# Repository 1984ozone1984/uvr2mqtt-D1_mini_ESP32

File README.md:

# UVR2MQTT - UVR1611 DL-Bus to MQTT Gateway

ESP32-based gateway that reads data from a Technische Alternative UVR1611 solar heating controller via DL-Bus and publishes to MQTT with Home Assistant auto-discovery.

## Hardware

- **Board**: Azdelivery D1 Mini ESP32 (ESP32-WROOM-32)
- **Connection**: DL-Bus via optocoupler to GPIO26
- **PCB Files**: KiCad schematic and PCB design files available in the `PCB/` folder, including Gerber files for manufacturing

## Features

### DL-Bus Protocol
- GPIO interrupt-based edge capture (bypasses RMT 512-symbol limitation)
- Dedicated high-priority interrupt on Core 1 (away from WiFi on Core 0)
- Manchester-like decoding with automatic polarity detection
- SYNC detection, checksum validation
- Full 64-byte frame parsing

### Sensor Data
- 16 temperature/flow/radiation sensors with configurable names
- 13 digital outputs (pumps, valves, mixers)
- 4 speed levels for variable-speed pumps
- 2 heat meters with power (kW) and energy (kWh)

### MQTT & Home Assistant
- WiFi connection with automatic reconnection
- MQTT client with Last Will and Testament (online/offline status)
- Home Assistant auto-discovery for all entities
- Configurable publish intervals
- Median filtering for sensor values
- Immediate publish on output state changes

### Web Configuration
- Built-in web UI for configuration (no rebuild required)
- WiFi STA/AP mode with automatic fallback
- Configure WiFi and MQTT settings via browser
- Edit all I/O names:
  - Sensor names (S1-S16)
  - Output names (A1-A13)
  - Speed level names (Drehzahlstufen A1, A2, A6, A7)
  - Heat meter names (WMZ1/WMZ2 power and energy)
- Disable entities by setting name to `---` or empty
- Live sensor and output status display
- Settings stored in NVS (persist across reboots)
- OTA firmware update via web browser

## Screenshots

### Web Interface - Status Page

### Live Sensor Data

### Output States

### WiFi Configuration

### MQTT Configuration

### Home Assistant Integration

## Configuration

### First Boot Setup (Web UI)

1. Flash the firmware to your ESP32
2. Device starts in AP mode (no credentials yet)
3. Connect to WiFi network **"UVR1611-XXXXXX"** (XXXXXX = last 6 chars of MAC address)
4. Open http://192.168.4.1 in your browser
5. Configure WiFi credentials and MQTT settings
6. Device saves settings and reboots
7. Device connects to your WiFi network
8. Access web UI via **http://uvr1611-gateway.local** or the device IP

### WiFi Modes

**STA Mode (Normal Operation)**:
- Connects to your configured WiFi network
- MQTT publishing active
- Web UI accessible at hostname.local

**AP Mode (Configuration/Fallback)**:
- Activates when no credentials or connection fails
- SSID: "UVR1611-XXXXXX"
- IP: 192.168.4.1
- Configure via web browser
- DL-Bus reading continues locally

### Configuring Sensors, Outputs, Speed Levels & Heat Meters

All I/O names are configurable via the web UI. **Only entities with configured names are published to MQTT and Home Assistant.** Use `---` or leave empty to disable an entity.

**Via Web UI (recommended):**
1. Go to the `/config` page
2. Scroll down to the I/O configuration section
3. Edit names for:
   - **Sensors S1-S16**: Temperature, flow, radiation sensors
   - **Outputs A1-A13**: Pumps, valves, mixers
   - **Speed Levels (Drehzahlstufen)**: Variable speed for A1, A2, A6, A7
   - **Heat Meters (Wärmemengenzähler)**: WMZ1/WMZ2 power (kW) and energy (kWh)
4. Click "Save I/O Names"
5. Changes take effect immediately for web display
6. **Reboot** to update MQTT topics and Home Assistant discovery

**Name Filtering:**
- Names must contain at least one letter or number to be published
- Names with only `-` characters (like `---`) are disabled
- Empty names are disabled
- Disabled entities do not appear in Home Assistant

**Example Configuration:**
| Entity | Name | Result |
|--------|------|--------|
| S1 | `T.Heizkr.VL` | ✅ Published |
| S10 | `---` | ❌ Disabled |
| S11 | ` ` (empty) | ❌ Disabled |
| WMZ1 Leistung | `Solar Leistung` | ✅ Published |
| WMZ2 Energie | `---` | ❌ Disabled |

**Via menuconfig (compile-time defaults):**
```bash
pio run -t menuconfig
```
Navigate to: "UVR1611 Configuration" → "Sensor Names", "Output Names", "Speed Level Names", or "Heat Meter Names"

### OTA Firmware Update

After initial USB flash, firmware can be updated via web browser:
1. Go to the `/config` page
2. Find "Firmware Update" section
3. Select new `.bin` firmware file
4. Click "Upload & Update Firmware"
5. Device reboots automatically with new firmware

## Building

Requires PlatformIO with ESP-IDF framework.

```bash
# Build
pio run

# Upload
pio run -t upload

# Monitor serial output
pio device monitor

# Configure sensor names
pio run -t menuconfig
```

## MQTT Topics

```
uvr1611/status                          # "online" / "offline" (LWT)
uvr1611/sensor/{sensor_name}/state      # Sensor value (median)
uvr1611/switch/{output_name}/state      # "ON" / "OFF"
uvr1611/sensor/{speed_name}/state       # Speed level (% or "inactive")
uvr1611/sensor/{hm_power_name}/state    # Heat meter power in kW
uvr1611/sensor/{hm_energy_name}/state   # Heat meter energy in kWh
uvr1611/system/mac                      # MAC address
uvr1611/system/ip                       # IP address
uvr1611/system/uptime                   # Uptime in seconds
```

Topic names are derived from configured names (lowercase, spaces/dots replaced with underscores).
Only entities with configured names (containing letters/numbers) are published.

## Home Assistant

Entities with configured names are automatically discovered via MQTT discovery. They appear under a single device with your configured hostname:
- Temperature sensors with proper device class
- Binary sensors for outputs (pumps, valves)
- Numeric sensors for speed levels (Drehzahlstufen)
- Power and energy sensors for heat meters (Wärmemengenzähler)
- System uptime sensor
- Diagnostic entities (IP address, MAC address, connectivity status)

**Note:** Only entities with names containing letters or numbers are registered. Use `---` to hide unused sensors/outputs from Home Assistant.

Change the device name by editing the hostname in the web UI and rebooting.

## Protocol Details

### DL-Bus Timing
- Display clock: 488 Hz
- Bit duration: 2.048 ms (2048 us)
- Half-bit duration: 1.024 ms (1024 us)

### Frame Structure
- SYNC: 16 high bits
- Data: 64 bytes (start bit + 8 data bits + stop bit per byte)
- Checksum: Sum of bytes 0-62 mod 256

### Sensor Types
| Type | Description | Encoding |
|------|-------------|----------|
| 0x00 | Unused | - |
| 0x10 | Digital | Bit 7 of high byte |
| 0x20 | Temperature | 12-bit signed, /10 for °C |
| 0x30 | Flow rate | 12-bit × 4 l/h |
| 0x60 | Radiation | 12-bit W/m² |
| 0x70 | Room sensor | 9-bit signed, /10 for °C |

## Architecture

```
GPIO26 (Core 1) ─► Edge Buffer ─► Bit Extractor ─► Manchester Decoder ─► Frame Queue
                                    (Core 1)          (Core 1)              │
                                                                            ▼
WiFi/MQTT (Core 0) ◄────────────────────────────────────────────── Main Loop
```

- DL-Bus capture runs entirely on Core 1 to avoid WiFi interference
- WiFi power save disabled for consistent interrupt timing
- Dedicated GPIO interrupt (not shared ISR service) for lower latency

## Status

**All Phases Complete**:
- DL-Bus decoding: 0.2% error rate
- All sensor types parsed correctly
- MQTT publishing working
- Home Assistant auto-discovery working
- Web-based configuration UI working
- WiFi STA/AP mode with auto-fallback working
- Sensor/output name editing via web UI
- OTA firmware update via web browser

## License

MIT

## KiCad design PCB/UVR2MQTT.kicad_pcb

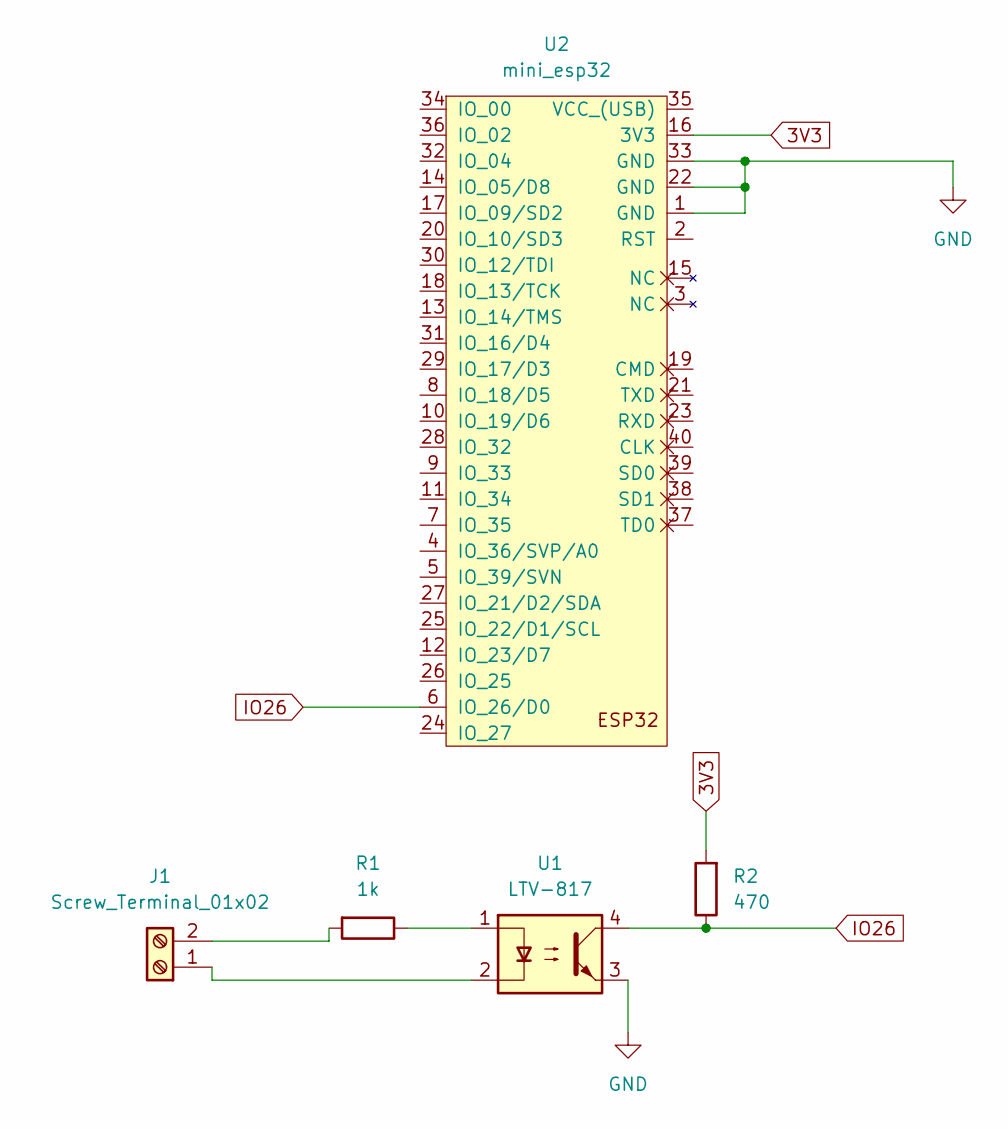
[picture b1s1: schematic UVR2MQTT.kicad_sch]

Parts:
J1: Screw_Terminal_01x02
R1: 1k; R_Axial_DIN0207_L6.3mm_D2.5mm_P10.16mm_Horizontal
R2: 470; R_Axial_DIN0207_L6.3mm_D2.5mm_P10.16mm_Horizontal
U1: LTV-817; DIP-4_W7.62mm
U2: mini_esp32; ESP32_mini

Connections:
3V3: R2.2, U2.16 (3V3)
GND: U1.3, U2.1 (GND), U2.22 (GND), U2.33 (GND)
IO26: R2.1, U1.4, U2.6 (IO_26/D0)
unnamed: J1.1, U1.2
unnamed: J1.2, R1.2
unnamed: R1.1, U1.1

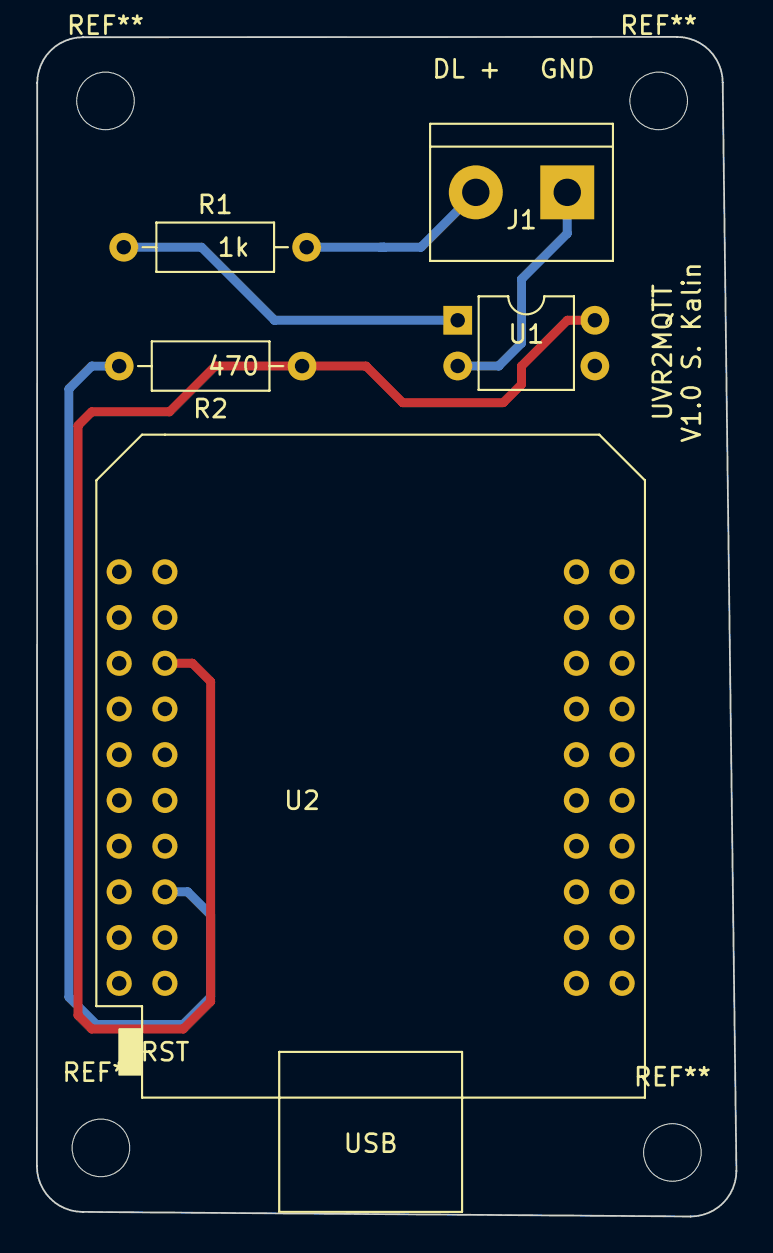
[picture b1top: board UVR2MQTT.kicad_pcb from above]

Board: 2 copper layers, 38.9 x 65.5 mm, 5 parts (0 on the bottom side), 6 nets.

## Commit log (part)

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2026-01-23 working DL-Bus decoding - Configuration - Wifi - MQTT publishing
2026-01-23 new Configuration settings
2026-01-24 Wifi STA/AP mode added - configuration via AP working
2026-01-24 compile Fehler behoben
2026-01-24 PCB files added
2026-01-24 Update DL-Bus decoding error rate in README
